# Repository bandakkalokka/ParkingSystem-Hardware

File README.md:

# ParkingSystem-Hardware
Hardware files for ENEL 400 parking system (KiCAD EDA)

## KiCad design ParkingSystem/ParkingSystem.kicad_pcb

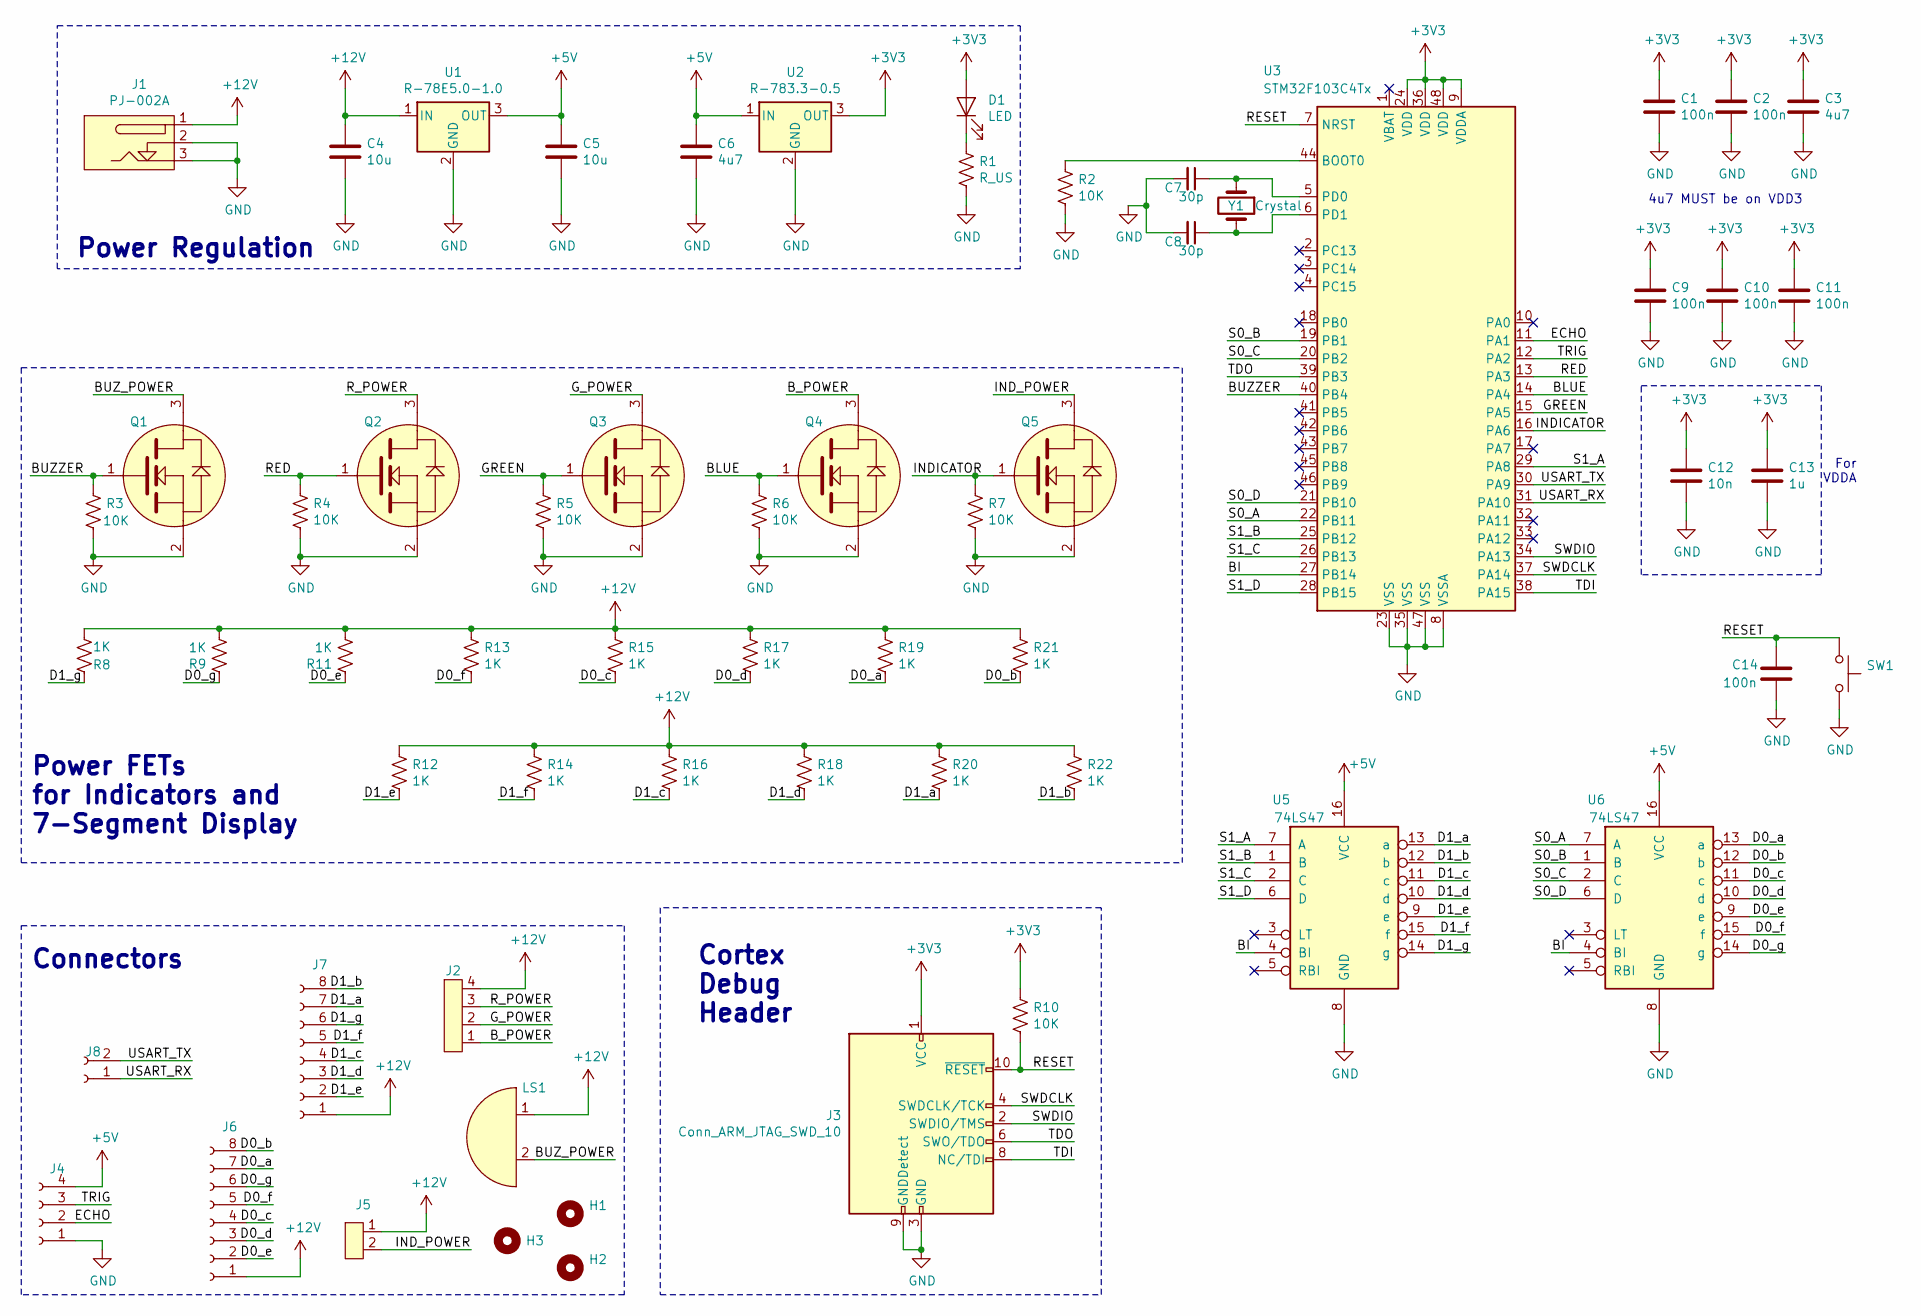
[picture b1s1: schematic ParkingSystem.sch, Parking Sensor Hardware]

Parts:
C1, C2, C9, C10, C11, C14: 100n; C_0603_1608Metric_Pad1.05x0.95mm_HandSolder
C3, C6: 4u7; C_0603_1608Metric_Pad1.05x0.95mm_HandSolder
C4, C5: 10u; C_0603_1608Metric_Pad1.05x0.95mm_HandSolder
C7, C8: 30p; C_0603_1608Metric_Pad1.05x0.95mm_HandSolder
C12: 10n; C_0603_1608Metric_Pad1.05x0.95mm_HandSolder
C13: 1u; C_0603_1608Metric_Pad1.05x0.95mm_HandSolder
D1: LED; LED_0603_1608Metric_Pad1.05x0.95mm_HandSolder
H1, H2, H3: MountingHole; MountingHole_4.3mm_M4_DIN965_Pad
J1: PJ-002A
J2: 0430450400; Molex_Micro-Fit_3.0_43045-0400_2x02_P3.00mm_Horizontal
J3: Conn_ARM_JTAG_SWD_10; PinHeader_2x05_P1.27mm_Vertical_SMD
J4: Conn_01x04_Female; PinSocket_1x04_P2.54mm_Horizontal
J5: 0430450200; Molex_Micro-Fit_3.0_43045-0200_2x01_P3.00mm_Horizontal
J6, J7: Conn_01x08_Female; Molex_Micro-Fit_3.0_43045-0800_2x04_P3.00mm_Horizontal
J8: Conn_01x02_Female; PinHeader_1x02_P2.54mm_Vertical
LS1: AI-2437-TWT-R
Q1, Q2, Q3, Q4, Q5: SSM3K333R,LF; SSM3K33R,LF
R1: R_US; R_0603_1608Metric_Pad1.05x0.95mm_HandSolder
R2, R3, R4, R5, R6, R7, R10: 10K; R_0603_1608Metric_Pad1.05x0.95mm_HandSolder
R8, R9, R11, R12, R13, R14, R15, R16, R17, R18, R19, R20, R21, R22: 1K; R_0603_1608Metric_Pad1.05x0.95mm_HandSolder
SW1: SW_Push; SW_SPST_B3S-1000
U1: R-78E5.0-1.0; Converter_DCDC_RECOM_R-78E-0.5_THT
U2: R-783.3-0.5; Converter_DCDC_RECOM_R-78E-0.5_THT
U3: STM32F103C4Tx; LQFP-48_7x7mm_P0.5mm
U5, U6: 74LS47; SN74LS47N
Y1: Crystal; Crystal_HC18-U_Vertical

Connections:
+3V3: C1.1, C2.1, C3.1, C9.1, C10.1, C11.1, C12.1, C13.1, D1.2 (A), J3.1 (VCC), R10.1, U2.3 (OUT), U3.9 (VDDA), U3.24 (VDD), U3.36 (VDD), U3.48 (VDD)
+5V: C5.1, C6.1, J4.4, U1.3 (OUT), U2.1 (IN), U5.16 (VCC), U6.16 (VCC)
+12V: C4.1, J1.1, J2.4, J5.1, J6.1, J7.1, LS1.1, R8.2, R9.2, R11.2, R12.1, R13.1, R14.1, R15.1, R16.1, R17.1, R18.1, R19.1, R20.1, R21.1, R22.1, U1.1 (IN)
/BI: U3.27 (PB14), U5.4 (BI), U6.4 (BI)
/BLUE: Q4.1, R6.1, U3.14 (PA4)
/BUZZER: Q1.1, R3.1, U3.40 (PB4)
/BUZ_POWER: LS1.2, Q1.3
/B_POWER: J2.1, Q4.3
/D0_a: J6.7, R19.2, U6.13 (a)
/D0_b: J6.8, R21.2, U6.12 (b)
/D0_c: J6.4, R15.2, U6.11 (c)
/D0_d: J6.3, R17.2, U6.10 (d)
/D0_e: J6.2, R11.1, U6.9 (e)
/D0_f: J6.5, R13.2, U6.15 (f)
/D0_g: J6.6, R9.1, U6.14 (g)
/D1_a: J7.7, R20.2, U5.13 (a)
/D1_b: J7.8, R22.2, U5.12 (b)
/D1_c: J7.4, R16.2, U5.11 (c)
/D1_d: J7.3, R18.2, U5.10 (d)
/D1_e: J7.2, R12.2, U5.9 (e)
/D1_f: J7.5, R14.2, U5.15 (f)
/D1_g: J7.6, R8.1, U5.14 (g)
/ECHO: J4.2, U3.11 (PA1)
/GREEN: Q3.1, R5.1, U3.15 (PA5)
/G_POWER: J2.2, Q3.3
/INDICATOR: Q5.1, R7.1, U3.16 (PA6)
/IND_POWER: J5.2, Q5.3
/RED: Q2.1, R4.1, U3.13 (PA3)
/RESET: C14.1, J3.10 (~RESET~), R10.2, SW1.1, U3.7 (NRST)
/R_POWER: J2.3, Q2.3
/S0_A: U3.22 (PB11), U6.7 (A)
/S0_B: U3.19 (PB1), U6.1 (B)
/S0_C: U3.20 (PB2), U6.2 (C)
/S0_D: U3.21 (PB10), U6.6 (D)
/S1_A: U3.29 (PA8), U5.7 (A)
/S1_B: U3.25 (PB12), U5.1 (B)
/S1_C: U3.26 (PB13), U5.2 (C)
/S1_D: U3.28 (PB15), U5.6 (D)
/SWDCLK: J3.4 (SWDCLK/TCK), U3.37 (PA14)
/SWDIO: J3.2 (SWDIO/TMS), U3.34 (PA13)
/TDI: J3.8 (NC/TDI), U3.38 (PA15)
/TDO: J3.6 (SWO/TDO), U3.39 (PB3)
/TRIG: J4.3, U3.12 (PA2)
/USART_RX: J8.1, U3.31 (PA10)
/USART_TX: J8.2, U3.30 (PA9)
GND: C1.2, C2.2, C3.2, C4.2, C5.2, C6.2, C7.2, C8.2, C9.2, C10.2, C11.2, C12.2, C13.2, C14.2, J1.2, J1.3, J3.3 (GND), J3.5 (GND), J3.9 (GNDDetect), J4.1, Q1.2, Q2.2, Q3.2, Q4.2, Q5.2, R1.2, R2.1, R3.2, R4.2, R5.2, R6.2, R7.2, SW1.2, U1.2 (GND), U2.2 (GND), U3.8 (VSSA), U3.23 (VSS), U3.35 (VSS), U3.47 (VSS), U5.8 (GND), U6.8 (GND)
unnamed: C7.1, U3.5 (PD0), Y1.1
unnamed: C8.1, U3.6 (PD1), Y1.2
unnamed: D1.1 (K), R1.1
unnamed: R2.2, U3.44 (BOOT0)

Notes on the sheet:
4u7 MUST be on VDD3
For VDDA
Power FETs for Indicators and 7-Segment Display
Cortex Debug Header
Connectors
Power Regulation

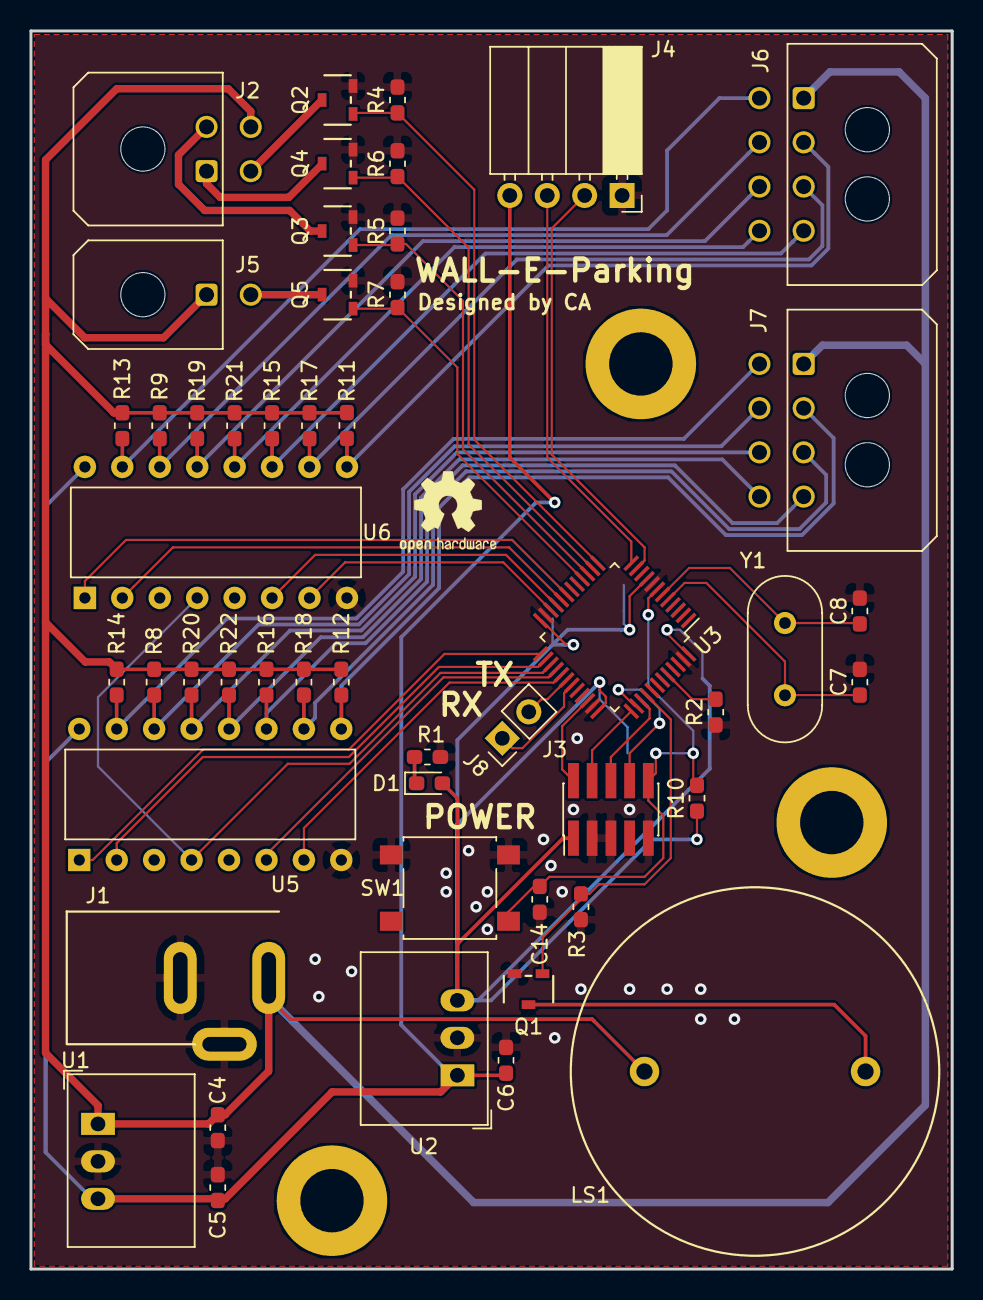
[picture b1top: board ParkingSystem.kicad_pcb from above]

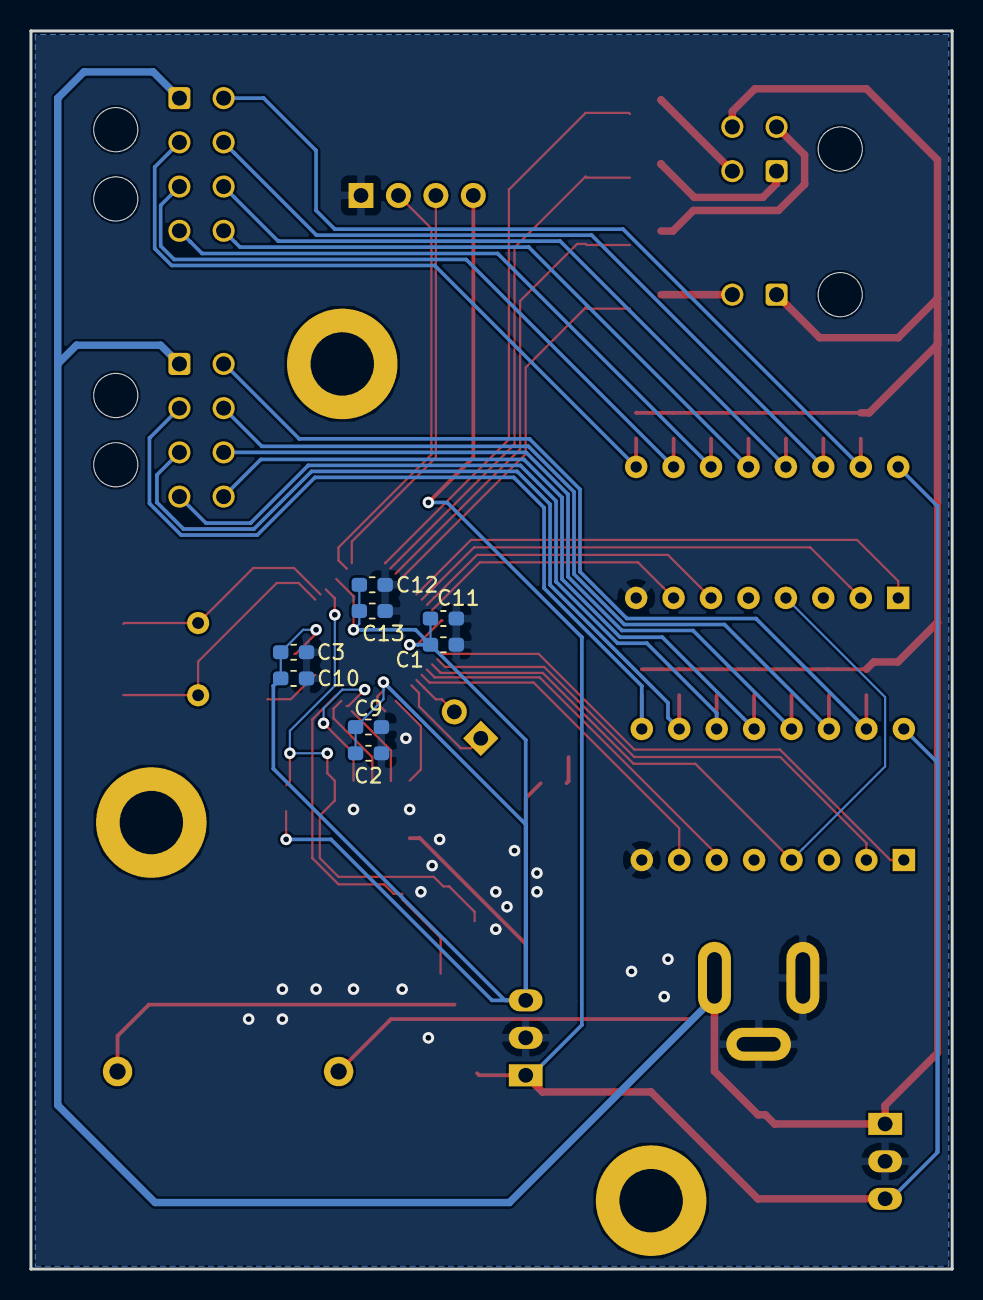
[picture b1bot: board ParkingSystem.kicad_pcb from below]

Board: 2 copper layers, 62.5 x 84.0 mm, 61 parts (8 on the bottom side), 50 nets.

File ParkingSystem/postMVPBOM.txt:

J5	430450200	Connectors:Molex_Micro-Fit_3.0_43045-0200_2x01_P3.00mm_Horizontal		yes
J2	430450400	Connectors:Molex_Micro-Fit_3.0_43045-0400_2x02_P3.00mm_Horizontal		yes
Reference	 Value	 Footprint	 Datasheet	have?
C1	100n	Capacitor_SMD:C_0603_1608Metric_Pad1.05x0.95mm_HandSolder	~	yes
C2	100n	Capacitor_SMD:C_0603_1608Metric_Pad1.05x0.95mm_HandSolder	~	yes
C9	100n	Capacitor_SMD:C_0603_1608Metric_Pad1.05x0.95mm_HandSolder	~	yes
C10	100n	Capacitor_SMD:C_0603_1608Metric_Pad1.05x0.95mm_HandSolder	~	yes
C11	100n	Capacitor_SMD:C_0603_1608Metric_Pad1.05x0.95mm_HandSolder	~	yes
C14	100n	Capacitor_SMD:C_0603_1608Metric_Pad1.05x0.95mm_HandSolder	~	yes
R4	10K	Resistor_SMD:R_0603_1608Metric_Pad1.05x0.95mm_HandSolder	~	yes
R5	10K	Resistor_SMD:R_0603_1608Metric_Pad1.05x0.95mm_HandSolder	~	yes
R6	10K	Resistor_SMD:R_0603_1608Metric_Pad1.05x0.95mm_HandSolder	~	yes
R7	10K	Resistor_SMD:R_0603_1608Metric_Pad1.05x0.95mm_HandSolder	~	yes
R3	10K	Resistor_SMD:R_0603_1608Metric_Pad1.05x0.95mm_HandSolder	~	yes
R2	10K	Resistor_SMD:R_0603_1608Metric_Pad1.05x0.95mm_HandSolder	~	yes
R10	10K	Resistor_SMD:R_0603_1608Metric_Pad1.05x0.95mm_HandSolder	~	yes
C12	10n	Capacitor_SMD:C_0603_1608Metric_Pad1.05x0.95mm_HandSolder	~	no
C4	10u	Capacitor_SMD:C_0603_1608Metric_Pad1.05x0.95mm_HandSolder	~	yes
C5	10u	Capacitor_SMD:C_0603_1608Metric_Pad1.05x0.95mm_HandSolder	~	yes
R8	1K	Resistor_SMD:R_0603_1608Metric_Pad1.05x0.95mm_HandSolder	~	no
R9	1K	Resistor_SMD:R_0603_1608Metric_Pad1.05x0.95mm_HandSolder	~	no
R11	1K	Resistor_SMD:R_0603_1608Metric_Pad1.05x0.95mm_HandSolder	~	no
R13	1K	Resistor_SMD:R_0603_1608Metric_Pad1.05x0.95mm_HandSolder	~	no
R15	1K	Resistor_SMD:R_0603_1608Metric_Pad1.05x0.95mm_HandSolder	~	no
R17	1K	Resistor_SMD:R_0603_1608Metric_Pad1.05x0.95mm_HandSolder	~	no
R19	1K	Resistor_SMD:R_0603_1608Metric_Pad1.05x0.95mm_HandSolder	~	no
R21	1K	Resistor_SMD:R_0603_1608Metric_Pad1.05x0.95mm_HandSolder	~	no
R12	1K	Resistor_SMD:R_0603_1608Metric_Pad1.05x0.95mm_HandSolder	~	no
R14	1K	Resistor_SMD:R_0603_1608Metric_Pad1.05x0.95mm_HandSolder	~	no
R16	1K	Resistor_SMD:R_0603_1608Metric_Pad1.05x0.95mm_HandSolder	~	no
R18	1K	Resistor_SMD:R_0603_1608Metric_Pad1.05x0.95mm_HandSolder	~	no
R20	1K	Resistor_SMD:R_0603_1608Metric_Pad1.05x0.95mm_HandSolder	~	no
R22	1K	Resistor_SMD:R_0603_1608Metric_Pad1.05x0.95mm_HandSolder	~	no
C13	1u	Capacitor_SMD:C_0603_1608Metric_Pad1.05x0.95mm_HandSolder	~	yes
C7	30p	Capacitor_SMD:C_0603_1608Metric_Pad1.05x0.95mm_HandSolder	~	yes
C8	30p	Capacitor_SMD:C_0603_1608Metric_Pad1.05x0.95mm_HandSolder	~	yes
C3	4u7	Capacitor_SMD:C_0603_1608Metric_Pad1.05x0.95mm_HandSolder	~	yes
C6	4u7	Capacitor_SMD:C_0603_1608Metric_Pad1.05x0.95mm_HandSolder	~	yes
U5	74LS47	Drivers:SN74LS47N	http://www.ti.com/lit/gpn/sn74LS47	no
U6	74LS47	Drivers:SN74LS47N	http://www.ti.com/lit/gpn/sn74LS47	no
LS1	AI-2437-TWT-R	Buzzers:AI-2437-TWT-R		yes
J8	Conn_01x02_Female	Connector_PinHeader_2.54mm:PinHeader_1x02_P2.54mm_Vertical	~	no
J4	Conn_01x04_Female	Connector_PinSocket_2.54mm:PinSocket_1x04_P2.54mm_Horizontal	~	yes
J7	Conn_01x08_Female	Connector_Molex:Molex_Micro-Fit_3.0_43045-0800_2x04_P3.00mm_Horizontal	~	no
J6	Conn_01x08_Female	Connector_Molex:Molex_Micro-Fit_3.0_43045-0800_2x04_P3.00mm_Horizontal	~	no
J3	Conn_ARM_JTAG_SWD_10	Connector_PinHeader_1.27mm:PinHeader_2x05_P1.27mm_Vertical_SMD	http://infocenter.arm.com/help/topic/com.arm.doc.faqs/attach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	yes
Y1	Crystal	Crystal:Crystal_HC18-U_Vertical	~	yes
D1	LED	LED_SMD:LED_0603_1608Metric_Pad1.05x0.95mm_HandSolder	~	yes
H2	MountingHole	MountingHole:MountingHole_4.3mm_M4_DIN965_Pad	~	
H1	MountingHole	MountingHole:MountingHole_4.3mm_M4_DIN965_Pad	~	
H3	MountingHole	MountingHole:MountingHole_4.3mm_M4_DIN965_Pad	~	
J1	PJ-002A	Connectors:PJ-002A		yes
R1	R_US	Resistor_SMD:R_0603_1608Metric_Pad1.05x0.95mm_HandSolder	~	NO
U2	R-783.3-0.5	Converter_DCDC:Converter_DCDC_RECOM_R-78E-0.5_THT	https://www.recom-power.com/pdf/Innoline/R-78xx-0.5.pdf	yes
U1	R-78E5.0-1.0	Converter_DCDC:Converter_DCDC_RECOM_R-78E-0.5_THT	https://www.recom-power.com/pdf/Innoline/R-78Exx-1.0.pdf	yes
Q1	"SSM3K333R,LF"	"MOSFETS:SSM3K33R,LF"		yes
Q2	"SSM3K333R,LF"	"MOSFETS:SSM3K33R,LF"		yes
Q3	"SSM3K333R,LF"	"MOSFETS:SSM3K33R,LF"		yes
Q4	"SSM3K333R,LF"	"MOSFETS:SSM3K33R,LF"		yes
Q5	"SSM3K333R,LF"	"MOSFETS:SSM3K33R,LF"		yes
U3	STM32F103C4Tx	Package_QFP:LQFP-48_7x7mm_P0.5mm	http://www.st.com/st-web-ui/static/active/en/resource/techni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	yes
SW1	SW_Push	Button_Switch_SMD:SW_SPST_B3S-1000		yes

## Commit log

2019-02-15 Schematic Capture started
2019-02-15 Add microfit footprints
2019-02-15 Add Cortex Programming Header
2019-02-15 Add Crystal Oscillator
2019-02-16 Schematic almost complete
2019-02-16 PCB Layout started
2019-02-16 Temporary part placement complete
2019-02-16 Move for better placement
2019-02-17 Change MCU pin I/O lines and route
2019-02-17 Preliminary Layout Complete
2019-02-17 Add Ground Pours
2019-02-17 Add Mounting Holes
2019-02-17 Add Dimensions and ground stitching
2019-02-17 Add few 3D Bodies, and more dimensions
2019-02-18 Add more dimensions
2019-02-18 Ground Stitching
2019-02-18 Schematic outline
2019-02-18 Barrel jack footprint change
2019-02-19 Generate Gerbers
2019-03-03 Generate new gerbers
2019-03-15 Add 7 Segment Drivers
2019-03-22 Add NMOS for 7 Seg
2019-03-23 Add 8-pin Molex for the 7-Seg
2019-03-23 Create sn74L47 footprint and begin pcb layout
2019-03-25 Add zones
2019-03-28 Generate gerbers and BOM
2019-03-28 Generate MVP Schematic
